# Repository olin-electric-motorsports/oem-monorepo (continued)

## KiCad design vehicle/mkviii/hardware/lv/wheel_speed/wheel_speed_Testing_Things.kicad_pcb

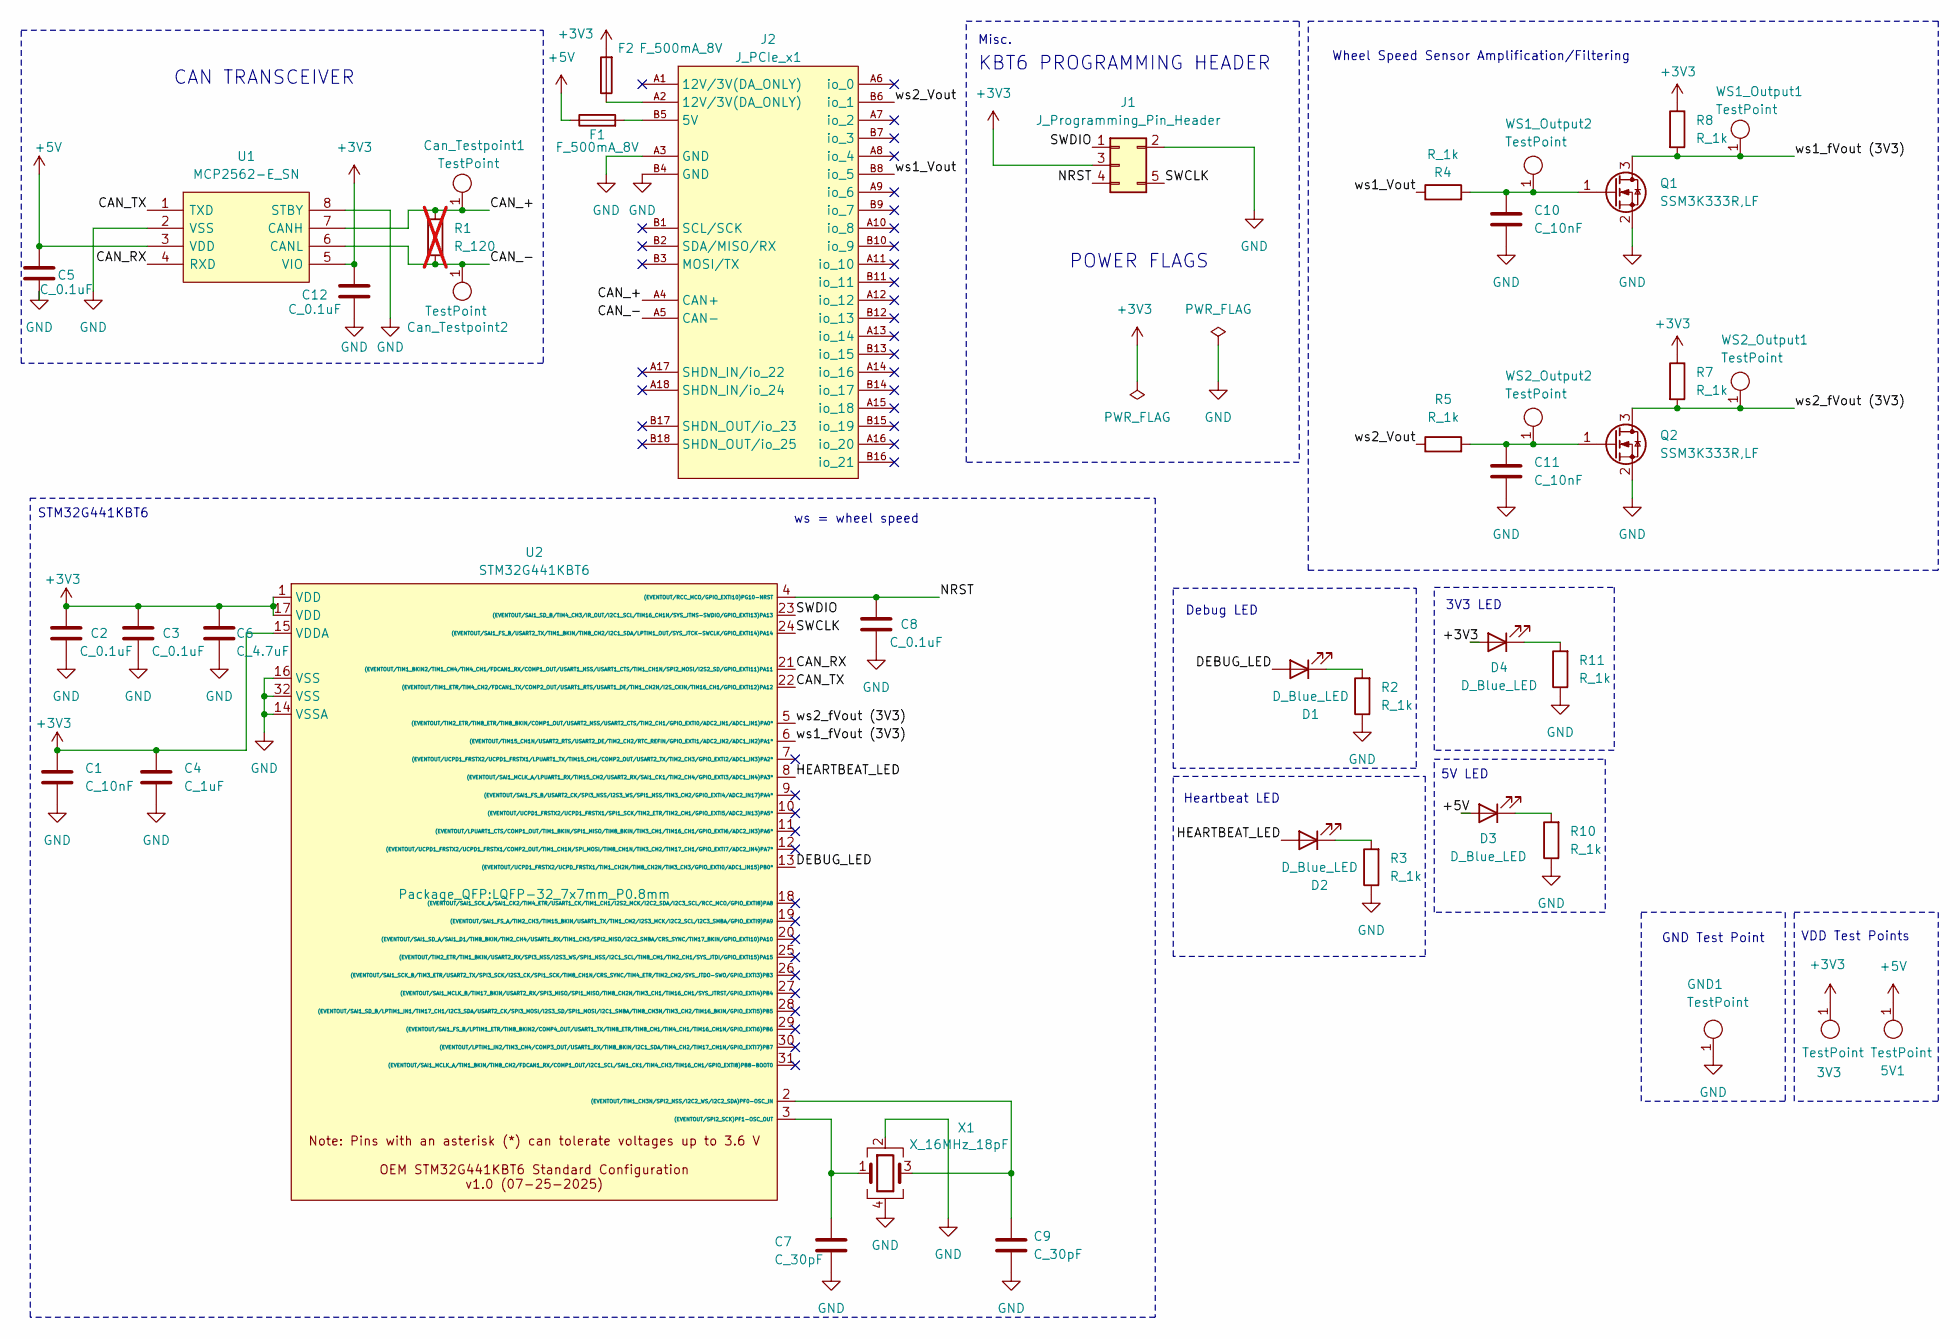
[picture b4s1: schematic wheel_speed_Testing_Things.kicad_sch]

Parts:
3V3, 5V1: TestPoint; TP_Hook_SMD; MPN 5019
C1, C10, C11: C_10nF; C_0603_1608Metric; MPN CL10B103KB8NNNC
C2, C3, C8: C_0.1uF; C_0603_1608Metric; MPN CL10B104KB8NNWC
C4: C_1uF; C_0603_1608Metric; MPN CL10B105KA8NNNC
C5, C12: C_0.1uF; C_0603_1608Metric; MPN C0603C104Z4VACTU
C6: C_4.7uF; C_0603_1608Metric; MPN GRT188R61E475ME13D
C7, C9: C_30pF; C_0603_1608Metric; MPN CML0603C0G300JT50V
Can_Testpoint1, Can_Testpoint2: TestPoint; TP_Hook_SMD; MPN 5019
D1, D2, D3, D4: D_Blue_LED; D_0805_2012Metric; MPN LTST-C171TBKT
F1, F2: F_500mA_8V; Fuse_1206_3216Metric; MPN 0ZCJ0050FF2G
GND1: TestPoint; TP_Hook_SMD; MPN 5019
J1: J_Programming_Pin_Header; J_Programming_Pin_Header_Keyed
J2: J_PCIe_x1; J_PCIe_x1_Key; MPN 2-1761465-1
Q1, Q2: SSM3K333R,LF; SOT-23-3
R1: R_120; R_0603_1608Metric; MPN RC0603FR-13120RL; not fitted
R2, R3, R4, R5, R7, R8, R10, R11: R_1k; R_0603_1608Metric; MPN RMCF0603FT1K00 (or ERJ-3GEYJ102V)
U1: MCP2562-E_SN; SOIC127P600X175-8N; Manufacturer_Part_Number MCP2562-E/SN; Mouser Part Number 579-MCP2562-E/SN
U2: STM32G441KBT6; LQFP-32_7x7mm_P0.8mm
WS1_Output1, WS1_Output2, WS2_Output1, WS2_Output2: TestPoint; TP_Hook_SMD; MPN 5019
X1: X_16MHz_18pF; FA238160000MBC0 (X_16MHz_18pF_SMD - FA-238_16.0000MB-C0); MPN FA-238 16.0000MB-C0

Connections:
+3V3: 3V3.1, C1.1, C2.1, C3.1, C4.1, C6.1, C12.2, D4.2 (A), F2.2, J1.3, R7.1, R8.1, U1.5 (VIO), U2.1 (VDD), U2.15 (VDDA), U2.17 (VDD)
+5V: 5V1.1, C5.2, D3.2 (A), F1.1, U1.3 (VDD)
/CAN_+: Can_Testpoint1.1, J2.A4 (CAN+), R1.1, U1.7 (CANH)
/CAN_-: Can_Testpoint2.1, J2.A5 (CAN-), R1.2, U1.6 (CANL)
/CAN_RX: U1.4 (RXD), U2.21 ((EVENTOUT/TIM1_BKIN2/TIM1_CH4/TIM4_CH1/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)
/CAN_TX: U1.1 (TXD), U2.22 ((EVENTOUT/TIM1_ETR/TIM4_CH2/FDCAN1_TX/C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)
/DEBUG_LED: D1.2 (A), U2.13 ((EVENTOUT/UCPD1_FRSTX2/UCPD_FRSTX1/TIM1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)
/HEARTBEAT_LED: D2.2 (A), U2.8 ((EVENTOUT/SAI1_MCLK_A/LPUART1_RX/TIM15_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)
/NRST: C8.1, J1.4, U2.4 ((EVENTOUT/RCC_MCO/GPIO_EXTI10)PG10-NRST)
/SWCLK: J1.5, U2.24 ((EVENTOUT/SAI1_FS_B/USART2_TX/TIM1_BKIN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)
/SWDIO: J1.1, U2.23 ((EVENTOUT/SAI1_SD_B/TIM4_CH3/IR_OUT/I2C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)
/ws1_Vout: J2.B8 (io_5), R4.1
/ws1_fVout (3V3): Q1.3 (D), R8.2, U2.6 ((EVENTOUT/TIM15_CH1N/USART2_RTS/USART2_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), WS1_Output1.1
/ws2_Vout: J2.B6 (io_1), R5.1
/ws2_fVout (3V3): Q2.3 (D), R7.2, U2.5 ((EVENTOUT/TIM2_ETR/TIM8_ETR/TIM8_BKIN/C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), WS2_Output1.1
GND: C1.2, C2.2, C3.2, C4.2, C5.1, C6.2, C7.2, C8.2, C9.2, C10.2, C11.2, C12.1, GND1.1, J1.2, J2.A3 (GND), J2.B4 (GND), Q1.2 (S), Q2.2 (S), R2.1, R3.1, R10.1, R11.1, U1.2 (VSS), U1.8 (STBY), U2.14 (VSSA), U2.16 (VSS), U2.32 (VSS), X1.2, X1.4
unnamed: D1.1 (K), R2.2
unnamed: D2.1 (K), R3.2
unnamed: D3.1 (K), R10.2
unnamed: D4.1 (K), R11.2
unnamed: F2.1, J2.A2 (12V/3V(DA_ONLY))
unnamed: F1.2, J2.B5 (5V)
unnamed: C10.1, Q1.1 (G), R4.2, WS1_Output2.1
unnamed: C11.1, Q2.1 (G), R5.2, WS2_Output2.1
unnamed: C7.1, U2.3 ((EVENTOUT/SPI2_SCK)PF1-OSC_OUT), X1.1
unnamed: C9.1, U2.2 ((EVENTOUT/TIM1_CH3N/SPI2_NSS/I2C2_WS/I2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), X1.3

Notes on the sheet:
Debug LED
Wheel Speed Sensor Amplification/Filtering
KBT6 PROGRAMMING HEADER
3V3 LED
ws = wheel speed
VDD Test Points
STM32G441KBT6
GND Test Point
Misc.
POWER FLAGS
5V LED
CAN TRANSCEIVER
Heartbeat LED

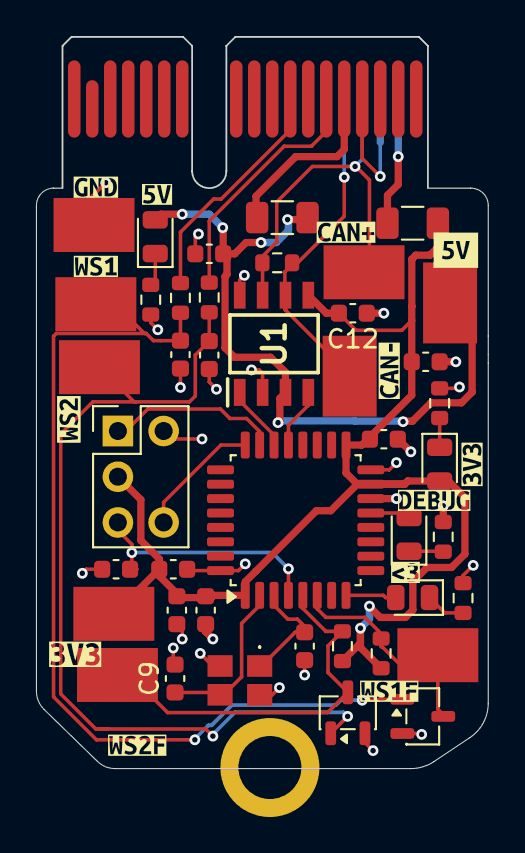
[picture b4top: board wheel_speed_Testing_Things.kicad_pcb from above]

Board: 2 copper layers, 25.1 x 40.6 mm, 57 parts (1 on the bottom side), 26 nets.

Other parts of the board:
kibuzzard-6AFB7296: G***; kibuzzard-6AFB7296
kibuzzard-6B0184AC: G***; kibuzzard-6B0184AC
kibuzzard-6B0184C3: G***; kibuzzard-6B0184C3
kibuzzard-6B0184D5: G***; kibuzzard-6B0184D5
kibuzzard-6B0184F9: G***; kibuzzard-6B0184F9
kibuzzard-6B0185A5: G***; kibuzzard-6B0185A5
kibuzzard-6B01848C: G***; kibuzzard-6B01848C
kibuzzard-6B01849E: G***; kibuzzard-6B01849E
kibuzzard-6B01852D: G***; kibuzzard-6B01852D
kibuzzard-6B01855D: G***; kibuzzard-6B01855D
kibuzzard-6B01859A: G***; kibuzzard-6B01859A
kibuzzard-6B018509: G***; kibuzzard-6B018509
kibuzzard-6B018514: G***; kibuzzard-6B018514
kibuzzard-6B018548: G***; kibuzzard-6B018548

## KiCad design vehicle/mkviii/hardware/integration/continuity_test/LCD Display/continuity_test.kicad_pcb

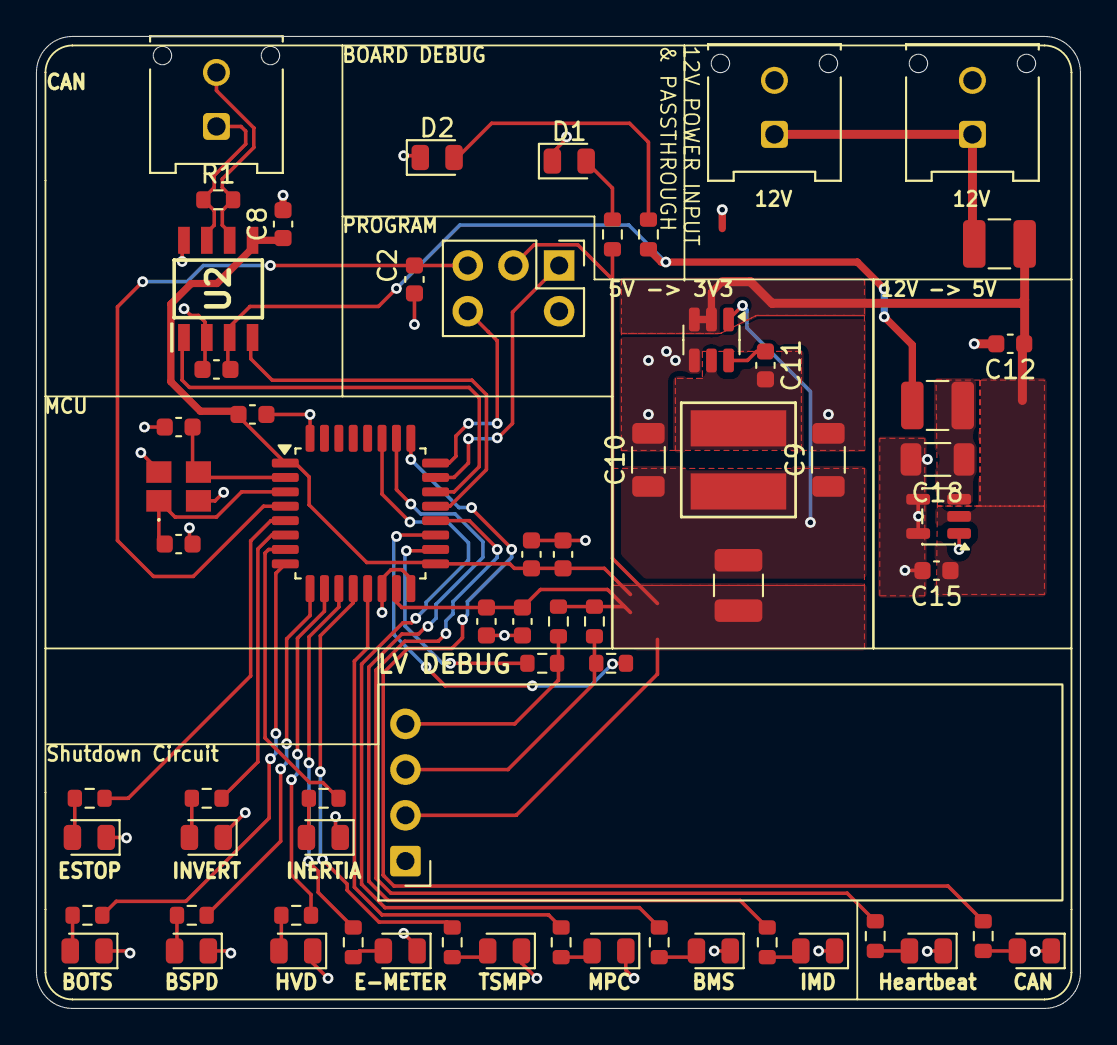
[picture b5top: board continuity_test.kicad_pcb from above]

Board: 2 copper layers, 58.0 x 54.0 mm, 65 parts (0 on the bottom side), 50 nets.

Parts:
C1, C2, C5, C6, C11: C_0.1uF; C_0603_1608Metric
C3: C_10nF; C_0603_1608Metric
C4: C_1uF; C_0603_1608Metric
C7: C_4.7uF; C_0603_1608Metric
C8, C15: C_0.1uF_16V; C_0603_1608Metric
C9, C10: C_22uF; C_1206_3216Metric
C12: C_10uF; C_0603_1608Metric
C13, C14: C_30pF; C_0603_1608Metric
C18: C_1uF; C_1206_3216Metric
D1: 3V3 POWER; D_0805_2012Metric
D2: 5V POWER; D_0805_2012Metric
D3, D4, D5, D6, D7, D8, D9, D10, D11, D12, D13, D14, D15: SOME_SHUTDOWN_NODE; D_0805_2012Metric
F1, F2, F3: F_500mA_16V; Fuse_1210_3225Metric
J1, J3, J4: Conn_01x02_Pin; Molex_Micro-Fit_3.0_43045-0212_2x01_P3.00mm_Vertical
J2: Programming_Pin_Header; J_Programming_Pin_Header_Keyed
L1: L_3.9uH; IND_BOURNS_SRR5018 (L_3.9uH_2A_55m_SMD)
R1: R_120; R_0603_1608Metric
R2, R3, R6, R7, R8, R9, R10, R11, R12, R13, R14, R15, R16, R17, R18: R_1K; R_0603_1608Metric
R4, R5: R_330_0.1W; R_0603_1608Metric
R19, R20: R_4.7k; R_0603_1608Metric
U1: STM32G441KBT6; LQFP-32_7x7mm_P0.8mm
U2: MCP2562-E_SN; SOIC127P600X175-8N
U3: AP63203WU-7; SOT-23-6
U4: TLV70450DBVR; SOT-23-5
U5: ER_OLEDM0.91_1x-I2C
Y1: X_Crystal_16MHz_18pF; FA238160000MBC0 (X_16MHz_18pF_SMD - FA-238_16.0000MB-C0)

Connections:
+3V3: C3.1, C4.1, C5.1, C6.1, C7.1, C8.1, F2.2, J2.3, R2.1, R19.1, R20.1, U1.1 (VDD), U1.15 (VDDA), U1.17 (VDD), U2.5 (VIO), U5.2 (VCC)
+5V: C1.2, F3.2, R3.1, U2.3 (VDD)
+12V: C12.1, C15.1, F1.1, U3.2 (EN), U3.3 (VIN), U4.2 (IN)
/CAN_+: J4.1, R1.1, U2.7 (CANH)
/CAN_-: J4.2, R1.2, U2.6 (CANL)
/CAN_RX: U1.21 ((FDCAN1_RX/GPIO_EXTI11)PA11), U2.4 (RXD)
/CAN_TX: U1.22 ((FDCAN1_TX/GPIO_EXTI12)PA12), U2.1 (TXD)
/I2C_SCL: R4.1, U1.19 ((TIM2_CH3/TIM15_BKIN/USART1_TX/GPIO_EXT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)
/I2C_SDA: R5.1, U1.18 ((TIM4_ETR/USART1_CK/GPIO_EXTI8)PA8)
/LED0: R6.1, U1.5 ((TIM2_ETR/TIM2_CH1/GPIO_EXTI0/ADC2_IN1/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)
/LED1: R7.1, U1.6 ((TIM15_CH1N/TIM2_CH2/GPIO_EXTI1/ADC2_IN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)
/LED2: R8.1, U1.7 ((TIM15_CH1/USART2_TX/TIM2_CH3/GPIO_EXTI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)
/LED3: R9.1, U1.8 ((TIM15_CH2/USART2_RX/TIM2_CH4/GPIO_EXTI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)
/LED4: R10.1, U1.9 ((USART2_CK/TIM3_CH2/GPIO_EXTI4/ADC2_IN1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)
/LED5: R11.1, U1.10 ((TIM2_ETR/TIM2_CH1/GPIO_EXTI5/ADC2_IN13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)
/LED6: R12.1, U1.11 ((TIM3_CH1/TIM16_CH1/GPIO_EXTI6/ADC2_IN3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)
/LED7: R13.1, U1.12 ((TIM3_CH2/TIM17_CH1/GPIO_EXTI7/ADC2_IN4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)
/LED8: R14.1, U1.13 ((TIM3_CH3/GPIO_EXTI0/ADC1_IN15)PB0*)
/LED9: R15.1, U1.27 ((TIM17_BKIN/SPI1_MISO/TIM3_CH1/TIM16_CH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)
/LED10: R16.1, U1.26 ((TIM3_ETR/SPI1_SCK/TIM4_ETR/TIM2_CH2/GP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)
/LED11: R17.1, U1.20 ((TIM2_CH4/USART1_RX/TIM17_BKIN/GPIO_EXT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)
/LED12: R18.1, U1.25 ((TIM2_ETR/TIM2_CH1/GPIO_EXTI15)PA15)
/NRST: C2.1, J2.4, U1.4 ((GPIO_EXTI10)PG10-NRST)
/SWCLK: J2.5, U1.24 ((SYS_JTCK-SWCLK/GPIO_EXTI14)PA14)
/SWDIO: J2.1, U1.23 ((SYS_JTMS-SWDIO/GPIO_EXTI13)PA13)
/V_INPUT: F1.2, J1.1, J3.1
GND: C1.1, C2.2, C3.2, C4.2, C5.2, C6.2, C7.2, C8.2, C9.2, C10.2, C12.2, C13.2, C14.2, C15.2, C18.2, D1.1 (K), D2.1 (K), D3.1 (K), D4.1 (K), D5.1 (K), D6.1 (K), D7.1 (K), D8.1 (K), D9.1 (K), D10.1 (K), D11.1 (K), D12.1 (K), D13.1 (K), D14.1 (K), D15.1 (K), J1.2, J2.2, J3.2, U1.14 (VSSA), U1.16 (VSS), U1.32 (VSS), U2.2 (VSS), U2.8 (STBY), U3.4 (GND), U4.1 (GND), U4.4 (NC_1), U4.5 (NC_2), U5.1 (GND), Y1.2, Y1.4
unnamed: D1.2 (A), R2.2
unnamed: D2.2 (A), R3.2
unnamed: D3.2 (A), R6.2
unnamed: D4.2 (A), R7.2
unnamed: D5.2 (A), R8.2
unnamed: D6.2 (A), R9.2
unnamed: D7.2 (A), R10.2
unnamed: D8.2 (A), R11.2
unnamed: D9.2 (A), R12.2
unnamed: D10.2 (A), R13.2
unnamed: D11.2 (A), R14.2
unnamed: D12.2 (A), R15.2
unnamed: D13.2 (A), R16.2
unnamed: D14.2 (A), R17.2
unnamed: D15.2 (A), R18.2
unnamed: C13.1, U1.2 (PF0-OSC_IN), Y1.3
unnamed: C14.1, U1.3 (PF1-OSC_OUT), Y1.1
unnamed: C11.1, U3.6 (BST)
unnamed: C9.1, C10.1, F2.1, L1.2, U3.1 (FB)
unnamed: C11.2, L1.1, U3.5 (SW)
unnamed: C18.1, F3.1, U4.3 (OUT)
unnamed: R4.2, R19.2, U5.3 (SCL)
unnamed: R5.2, R20.2, U5.4 (SDA)

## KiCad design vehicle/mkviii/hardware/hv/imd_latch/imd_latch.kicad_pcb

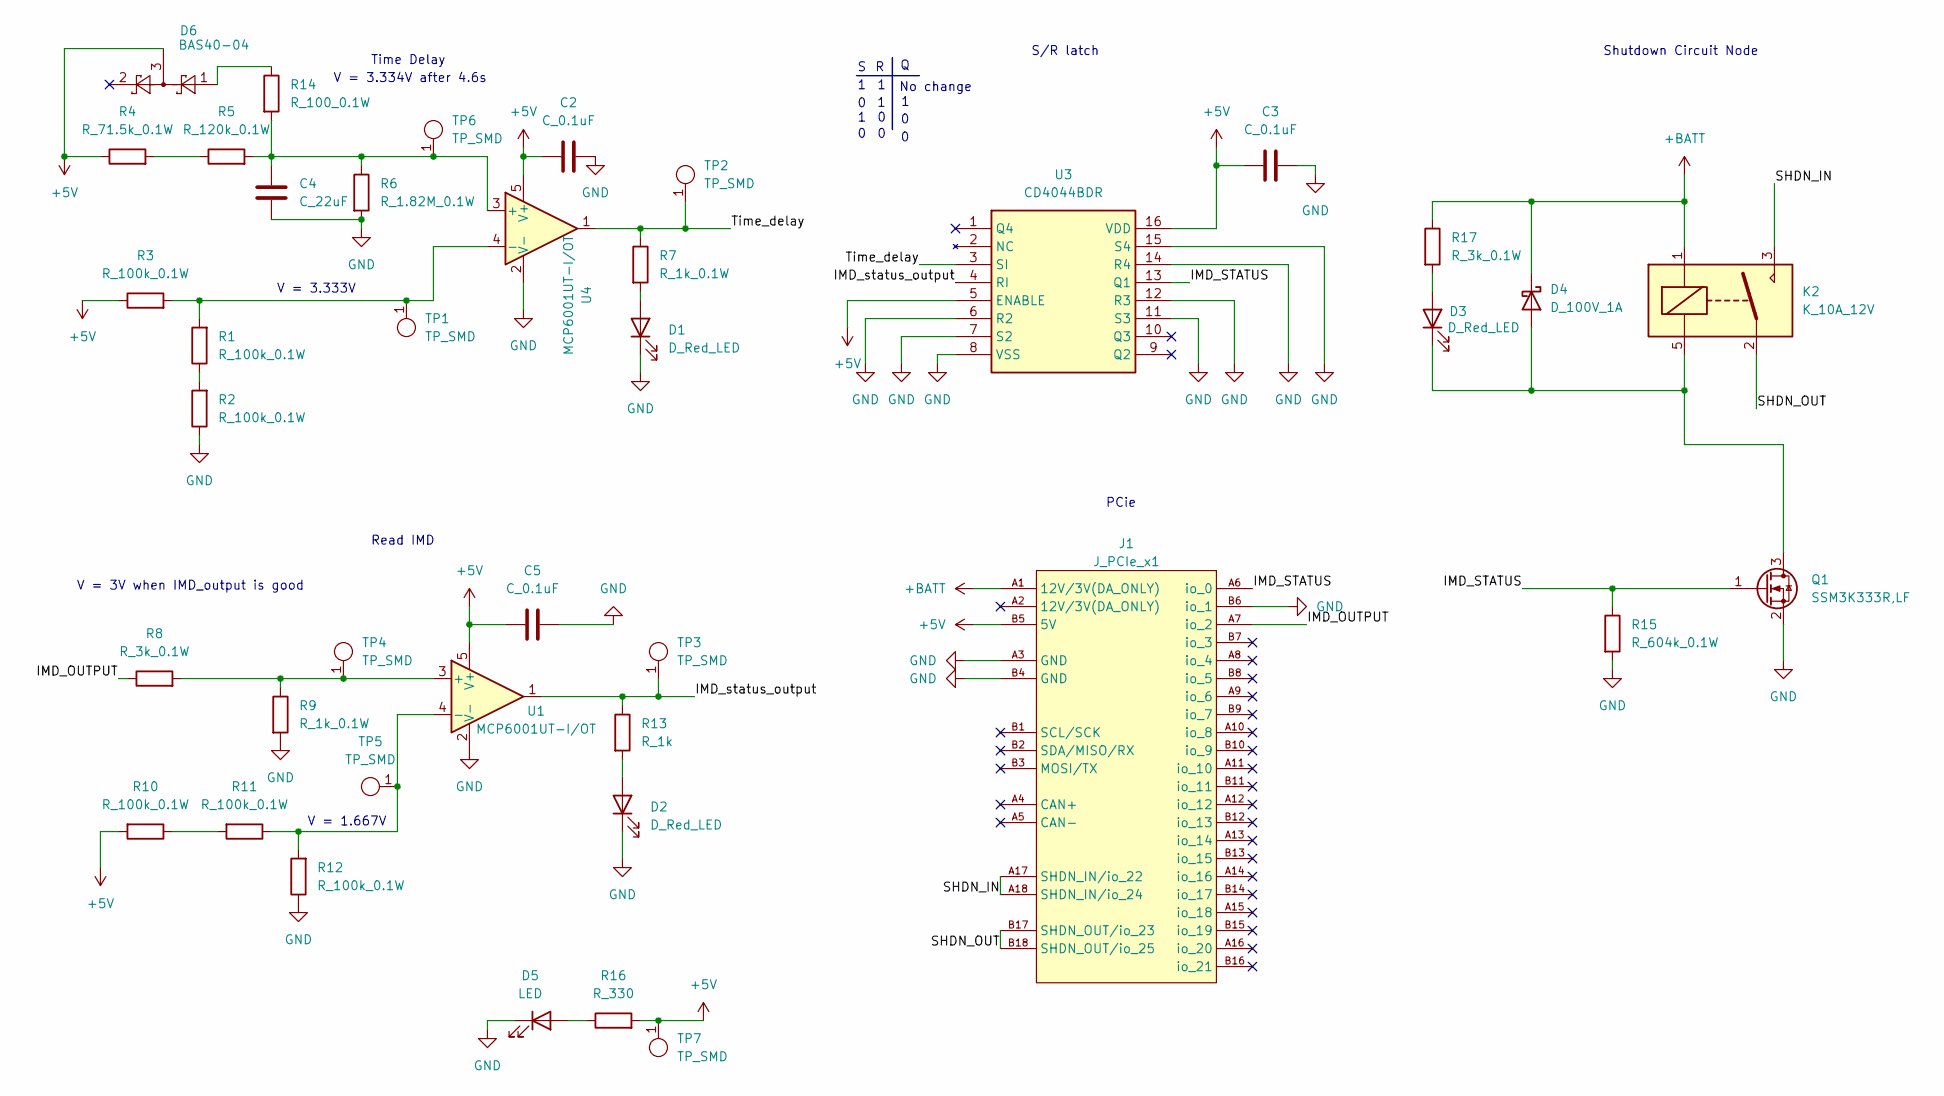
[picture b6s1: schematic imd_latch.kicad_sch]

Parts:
C2, C3, C5: C_0.1uF; C_0603_1608Metric; MPN C0603C104Z4VACTU
C4: C_22uF; C_1206_3216Metric; MPN CL31A226KAHNNNE
D1, D2, D3: D_Red_LED; D_0805_2012Metric; MPN LTST-C171KRKT
D4: D_100V_1A; SODFL3718X102N (D_Schottky_100V_1A_SMD - SS110LW); MPN SS110LW
D5: LED; D_0805_2012Metric; MPN QBLP631-IW
D6: BAS40-04; SOT-23
J1: J_PCIe_x1; J_PCIe_x1_Key; MPN 2-1761465-1
K2: K_10A_12V; G5Q1A4DC24 (K_SPST-NO_10A_12V_TH - G5Q-1A4-DC12); MPN G5Q-1A4 DC12
Q1: SSM3K333R,LF; SOT-23-3
R1, R2, R3, R10, R11, R12: R_100k_0.1W; R_0603_1608Metric; MPN RMCF0603FT100K
R4: R_71.5k_0.1W; R_0603_1608Metric; MPN RMCF0603FT71K5
R5: R_120k_0.1W; R_0603_1608Metric; MPN RC0603FR-13120KL
R6: R_1.82M_0.1W; R_0603_1608Metric; MPN RMCF0603FT1M82
R7, R9: R_1k_0.1W; R_0603_1608Metric; MPN RMCF0603FT1K00 (or ERJ-3GEYJ102V)
R8, R17: R_3k_0.1W; R_0603_1608Metric; MPN RC0603FR-103KL
R13: R_1k; R_0603_1608Metric; MPN RMCF0603FT1K00 (or ERJ-3GEYJ102V)
R14: R_100_0.1W; R_0603_1608Metric; MPN RMCF0603FT100R
R15: R_604k_0.1W; R_0603_1608Metric; MPN RMCF0603FT604K
R16: R_330; R_0603_1608Metric; MPN RMCF0603FT330R (or WR06X3300FTL)
TP1, TP2, TP3, TP4, TP5, TP6, TP7: TP_SMD; TP_Hook_SMD; MPN 5019
U1, U4: MCP6001UT-I/OT; SOT-23-5; MPN MCP6001UT-I/OT
U3: CD4044BDR; SOIC127P600X175-16N (U_Quad-NAND-RS-Latch_CD4044BDR_16-SOIC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; MPN CD4044BDR

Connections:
+5V: C2.1, C3.1, C5.2, D6.3, J1.B5 (5V), R3.1, R4.1, R10.2, R16.2, TP7.1, U1.5 (V+), U3.5 (ENABLE), U3.16 (VDD), U4.5 (V+)
+BATT: D4.1 (K), J1.A1 (12V/3V(DA_ONLY)), K2.1, R17.1
/<NO NET>: J1.A7 (io_2), R8.1
/IMD_STATUS: J1.A6 (io_0), Q1.1 (G), R15.1, U3.13 (Q1)
/IMD_status_output: R13.1, TP3.1, U1.1, U3.4 (RI)
/SHDN_IN: J1.A17 (SHDN_IN/io_22), J1.A18 (SHDN_IN/io_24), K2.3
/SHDN_OUT: J1.B17 (SHDN_OUT/io_23), J1.B18 (SHDN_OUT/io_25), K2.2
/Time_delay: R7.1, TP2.1, U3.3 (SI), U4.1
GND: C2.2, C3.2, C4.2, C5.1, D1.1 (K), D2.1 (K), D5.1 (K), J1.A3 (GND), J1.B4 (GND), J1.B6 (io_1), Q1.2 (S), R2.1, R6.2, R9.2, R12.1, R15.2, U1.2 (V-), U3.6 (R2), U3.7 (S2), U3.8 (VSS), U3.11 (S3), U3.12 (R3), U3.14 (R4), U3.15 (S4), U4.2 (V-)
unnamed: D1.2 (A), R7.2
unnamed: D2.2 (A), R13.2
unnamed: D3.2 (A), R17.2
unnamed: D3.1 (K), D4.2 (A), K2.5, Q1.3 (D)
unnamed: D5.2 (A), R16.1
unnamed: D6.1, R14.1
unnamed: R1.1, R2.2
unnamed: R4.2, R5.1
unnamed: R10.1, R11.2
unnamed: R8.2, R9.1, TP4.1, U1.3 (+)
unnamed: R11.1, R12.2, TP5.1, U1.4 (-)
unnamed: C4.1, R5.2, R6.1, R14.2, TP6.1, U4.3 (+)
unnamed: R1.2, R3.2, TP1.1, U4.4 (-)

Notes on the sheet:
Shutdown Circuit Node
S/R latch
No change
V = 3.334V after 4.6s
Time Delay
Read IMD
PCie
V = 3.333V
V = 3V when IMD_output is good
V = 1.667V

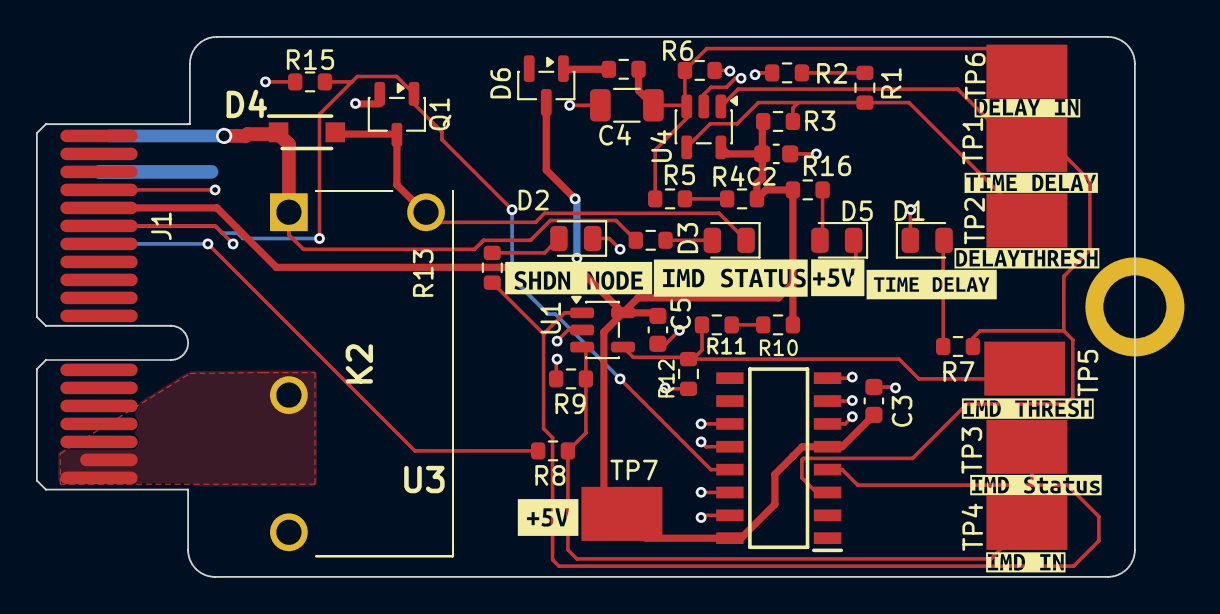
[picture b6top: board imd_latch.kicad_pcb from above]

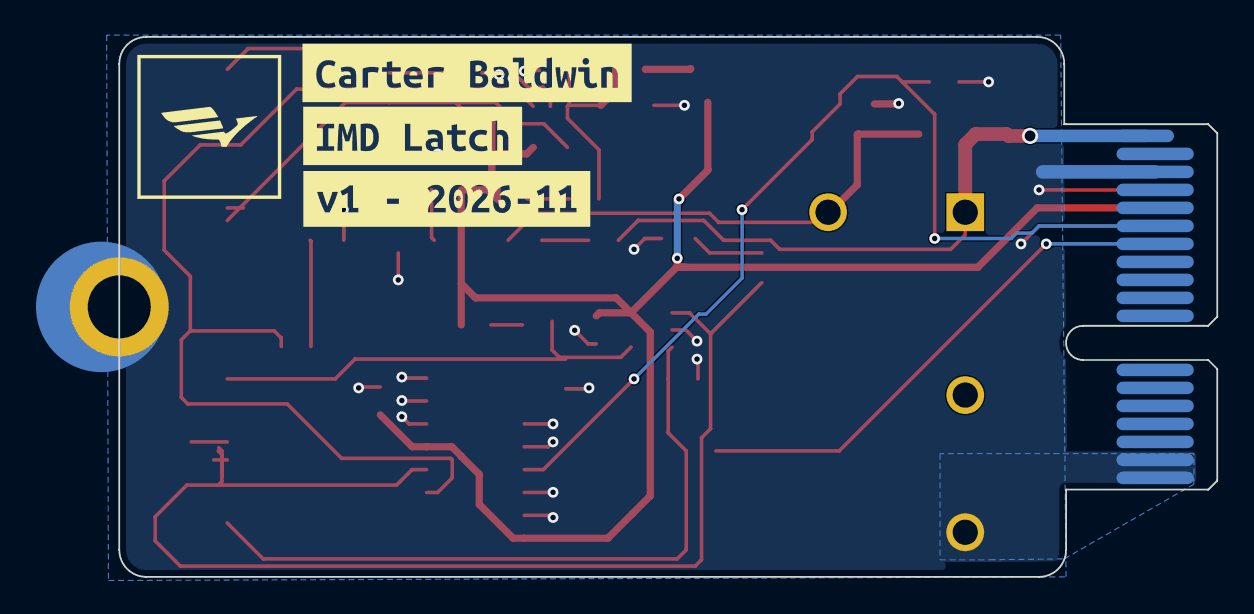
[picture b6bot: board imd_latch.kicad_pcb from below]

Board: 2 copper layers, 61.0 x 30.0 mm, 54 parts (3 on the bottom side), 22 nets.

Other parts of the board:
kibuzzard-6AFBBCFF: G***; kibuzzard-6AFBBCFF
kibuzzard-6AFCD9A5: G***; kibuzzard-6AFCD9A5
kibuzzard-6AFDBAFF: G***; kibuzzard-6AFDBAFF
kibuzzard-6AFDBEA3: G***; kibuzzard-6AFDBEA3
kibuzzard-6AFDC0E0: G***; kibuzzard-6AFDC0E0
kibuzzard-6AFDC1E5: G***; kibuzzard-6AFDC1E5
kibuzzard-6AFDC9E2: G***; kibuzzard-6AFDC9E2
kibuzzard-6AFDC9E7: G***; kibuzzard-6AFDC9E7
kibuzzard-6AFDC12F: G***; kibuzzard-6AFDC12F
kibuzzard-6AFDC58C: G***; kibuzzard-6AFDC58C
kibuzzard-6AFDC564: G***; kibuzzard-6AFDC564
kibuzzard-6AFDC608: G***; kibuzzard-6AFDC608
kibuzzard-6AFDCAAF: G***; kibuzzard-6AFDCAAF
kibuzzard-6B015E83: G***; kibuzzard-6B015E83

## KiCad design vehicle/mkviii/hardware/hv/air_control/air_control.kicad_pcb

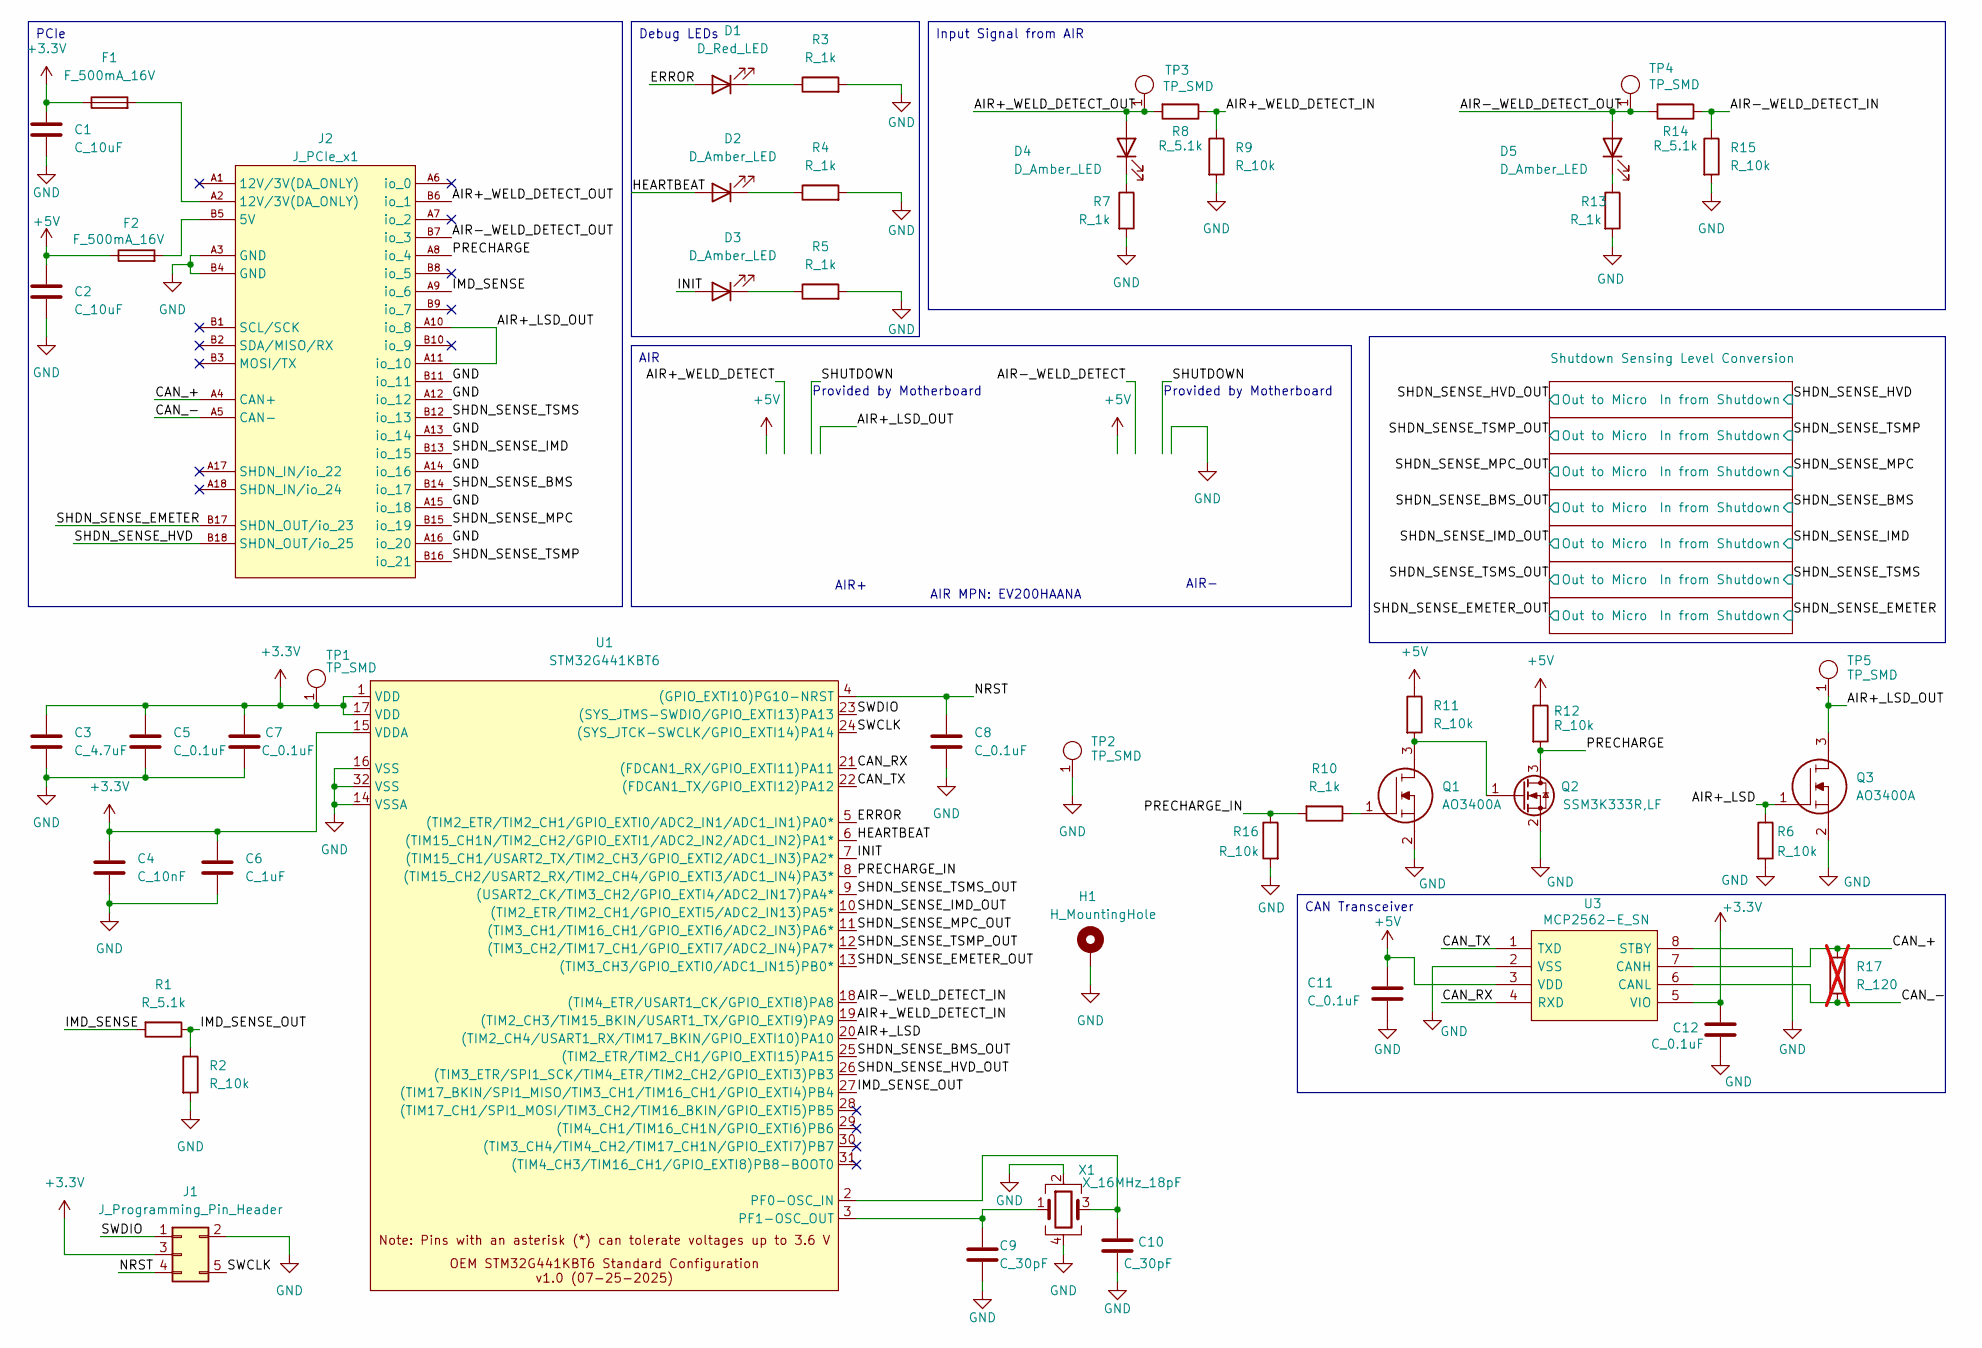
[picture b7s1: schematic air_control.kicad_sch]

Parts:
C1, C2: C_10uF; C_0603_1608Metric; MPN GRM188D71A106KA73D
C3: C_4.7uF; C_0603_1608Metric; MPN GRT188R61E475ME13D
C4: C_10nF; C_0603_1608Metric; MPN CL10B103KB8NNNC
C5, C7, C8, C11, C12: C_0.1uF; C_0603_1608Metric; MPN CL10B104KB8NNWC
C6: C_1uF; C_0603_1608Metric; MPN CL10B105KA8NNNC
C9, C10: C_30pF; C_0603_1608Metric; MPN CML0603C0G300JT50V
D1: D_Red_LED; D_0805_2012Metric; MPN LTST-C171KRKT
D2, D3, D4, D5: D_Amber_LED; D_0805_2012Metric; MPN LTST-C171AKT
F1, F2: F_500mA_16V; Fuse_1210_3225Metric; MPN 0ZCH0050FF2G
H1: H_MountingHole
J1: J_Programming_Pin_Header; J_Programming_Pin_Header_Keyed
J2: J_PCIe_x1; J_PCIe_x1_Key; MPN 2-1761465-1
Q1, Q3: AO3400A; Q_MOSFET_AO3400A; Manufacturer_Part_Number AO3400A
Q2: SSM3K333R,LF; SOT-23-3
R1, R8, R14: R_5.1k; R_0603_1608Metric; MPN CR0603AFX-5101EAS
R2, R6, R9, R11, R12, R15, R16: R_10k; R_0603_1608Metric; MPN RMCF0603FT10K0
R3, R4, R5, R7, R10, R13: R_1k; R_0603_1608Metric; MPN RMCF0603FT1K00 (or ERJ-3GEYJ102V)
R17: R_120; R_0603_1608Metric; MPN RC0603FR-13120RL; not fitted
TP1, TP2, TP3, TP4, TP5: TP_SMD; TP_Hook_SMD; MPN 5019
U1: STM32G441KBT6; LQFP-32_7x7mm_P0.8mm
U3: MCP2562-E_SN; SOIC127P600X175-8N; Manufacturer_Part_Number MCP2562-E/SN; Mouser Part Number 579-MCP2562-E/SN
X1: X_16MHz_18pF; FA238160000MBC0 (X_16MHz_18pF_SMD - FA-238_16.0000MB-C0); MPN FA-238 16.0000MB-C0

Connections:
+3.3V: C1.1, C3.1, C4.1, C5.1, C6.1, C7.1, C12.1, F1.1, J1.3, TP1.1, U1.1 (VDD), U1.15 (VDDA), U1.17 (VDD), U3.5 (VIO); also elsewhere on the board
+5V: C2.1, C11.1, F2.1, R11.1, R12.1, U3.3 (VDD)
/AIR+_LSD: Q3.1, R6.1, U1.20 ((TIM2_CH4/USART1_RX/TIM17_BKIN/GPIO_EXT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)
/AIR+_LSD_OUT: J2.A10 (io_8), J2.A11 (io_10), Q3.3, TP5.1
/AIR+_WELD_DETECT_IN: R8.1, R9.1, U1.19 ((TIM2_CH3/TIM15_BKIN/USART1_TX/GPIO_EXT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)
/AIR+_WELD_DETECT_OUT: D4.2 (A), J2.B6 (io_1), R8.2, TP3.1
/AIR-_WELD_DETECT_IN: R14.1, R15.1, U1.18 ((TIM4_ETR/USART1_CK/GPIO_EXTI8)PA8)
/AIR-_WELD_DETECT_OUT: D5.2 (A), J2.B7 (io_3), R14.2, TP4.1
/CAN_+: J2.A4 (CAN+), R17.1, U3.7 (CANH)
/CAN_-: J2.A5 (CAN-), R17.2, U3.6 (CANL)
/CAN_RX: U1.21 ((FDCAN1_RX/GPIO_EXTI11)PA11), U3.4 (RXD)
/CAN_TX: U1.22 ((FDCAN1_TX/GPIO_EXTI12)PA12), U3.1 (TXD)
/ERROR: D1.2 (A), U1.5 ((TIM2_ETR/TIM2_CH1/GPIO_EXTI0/ADC2_IN1/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)
/HEARTBEAT: D2.2 (A), U1.6 ((TIM15_CH1N/TIM2_CH2/GPIO_EXTI1/ADC2_IN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)
/IMD_SENSE: J2.A9 (io_6), R1.2
/IMD_SENSE_OUT: R1.1, R2.1, U1.27 ((TIM17_BKIN/SPI1_MISO/TIM3_CH1/TIM16_CH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)
/INIT: D3.2 (A), U1.7 ((TIM15_CH1/USART2_TX/TIM2_CH3/GPIO_EXTI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)
/NRST: C8.1, J1.4, U1.4 ((GPIO_EXTI10)PG10-NRST)
/PRECHARGE: J2.A8 (io_4), Q2.3 (D), R12.2
/PRECHARGE_IN: R10.2, R16.1, U1.8 ((TIM15_CH2/USART2_RX/TIM2_CH4/GPIO_EXTI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)
/SHDN_SENSE_BMS: J2.B14 (io_17); also elsewhere on the board
/SHDN_SENSE_BMS_OUT: U1.25 ((TIM2_ETR/TIM2_CH1/GPIO_EXTI15)PA15); also elsewhere on the board
/SHDN_SENSE_EMETER: J2.B17 (SHDN_OUT/io_23); also elsewhere on the board
/SHDN_SENSE_EMETER_OUT: U1.13 ((TIM3_CH3/GPIO_EXTI0/ADC1_IN15)PB0*); also elsewhere on the board
/SHDN_SENSE_HVD: J2.B18 (SHDN_OUT/io_25); also elsewhere on the board
/SHDN_SENSE_HVD_OUT: U1.26 ((TIM3_ETR/SPI1_SCK/TIM4_ETR/TIM2_CH2/GP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); also elsewhere on the board
/SHDN_SENSE_IMD: J2.B13 (io_15); also elsewhere on the board
/SHDN_SENSE_IMD_OUT: U1.10 ((TIM2_ETR/TIM2_CH1/GPIO_EXTI5/ADC2_IN13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); also elsewhere on the board
/SHDN_SENSE_MPC: J2.B15 (io_19); also elsewhere on the board
/SHDN_SENSE_MPC_OUT: U1.11 ((TIM3_CH1/TIM16_CH1/GPIO_EXTI6/ADC2_IN3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); also elsewhere on the board
/SHDN_SENSE_TSMP: J2.B16 (io_21); also elsewhere on the board
/SHDN_SENSE_TSMP_OUT: U1.12 ((TIM3_CH2/TIM17_CH1/GPIO_EXTI7/ADC2_IN4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); also elsewhere on the board
/SHDN_SENSE_TSMS: J2.B12 (io_13); also elsewhere on the board
/SHDN_SENSE_TSMS_OUT: U1.9 ((USART2_CK/TIM3_CH2/GPIO_EXTI4/ADC2_IN1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); also elsewhere on the board
/SWCLK: J1.5, U1.24 ((SYS_JTCK-SWCLK/GPIO_EXTI14)PA14)
/SWDIO: J1.1, U1.23 ((SYS_JTMS-SWDIO/GPIO_EXTI13)PA13)
GND: C1.2, C2.2, C3.2, C4.2, C5.2, C6.2, C7.2, C8.2, C9.2, C10.2, C11.2, C12.2, H1.1 (1_1), J1.2, J2.A3 (GND), J2.A12 (io_12), J2.A13 (io_14), J2.A14 (io_16), J2.A15 (io_18), J2.A16 (io_20), J2.B4 (GND), J2.B11 (io_11), Q1.2, Q2.2 (S), Q3.2, R2.2, R3.2, R4.2, R5.2, R6.2, R7.2, R9.2, R13.2, R15.2, R16.2, TP2.1, U1.14 (VSSA), U1.16 (VSS), U1.32 (VSS), U3.2 (VSS), U3.8 (STBY), X1.2, X1.4; also elsewhere on the board
unnamed: D1.1 (K), R3.1
unnamed: D2.1 (K), R4.1
unnamed: D3.1 (K), R5.1
unnamed: D4.1 (K), R7.1
unnamed: D5.1 (K), R13.1
unnamed: F1.2, J2.A2 (12V/3V(DA_ONLY))
unnamed: F2.2, J2.B5 (5V)
unnamed: Q1.1, R10.1
unnamed: Q1.3, Q2.1 (G), R11.2
unnamed: C10.1, U1.2 (PF0-OSC_IN), X1.3
unnamed: C9.1, U1.3 (PF1-OSC_OUT), X1.1

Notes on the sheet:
AIR MPN: EV200HAANA
Provided by Motherboard
AIR+
AIR-
AIR
Debug LEDs
Input Signal from AIR
PCIe
CAN Transceiver

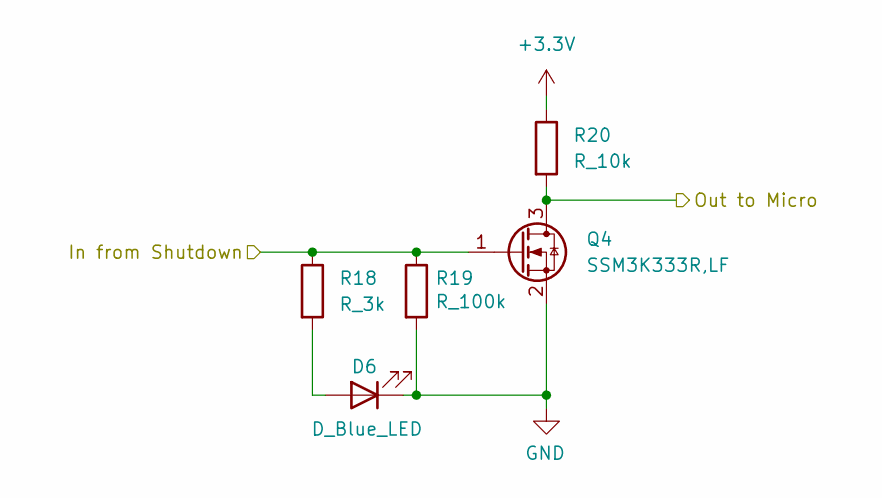
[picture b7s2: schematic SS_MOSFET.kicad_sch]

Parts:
D6: D_Blue_LED; D_0805_2012Metric; MPN LTST-C171TBKT
Q4: SSM3K333R,LF; SOT-23-3
R18: R_3k; R_0603_1608Metric; MPN RC0603FR-103KL
R19: R_100k; R_0603_1608Metric; MPN RMCF0603FT100K
R20: R_10k; R_0603_1608Metric; MPN RMCF0603FT10K0

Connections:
+3.3V: R20.1; also elsewhere on the board
/SHDN_SENSE_TSMP: Q4.1 (G), R18.1, R19.1; also elsewhere on the board
/SHDN_SENSE_TSMP_OUT: Q4.3 (D), R20.2; also elsewhere on the board
GND: D6.1 (K), Q4.2 (S), R19.2; also elsewhere on the board
unnamed: D6.2 (A), R18.2

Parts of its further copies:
D7, D8, D9, D10, D11, D12: D_Blue_LED; D_0805_2012Metric; MPN LTST-C171TBKT
Q5, Q6, Q7, Q8, Q9, Q10: SSM3K333R,LF; SOT-23-3
R21, R24, R27, R30, R33, R36: R_3k; R_0603_1608Metric; MPN RC0603FR-103KL
R22, R25, R28, R31, R34, R37: R_100k; R_0603_1608Metric; MPN RMCF0603FT100K
R23, R26, R29, R32, R35, R38: R_10k; R_0603_1608Metric; MPN RMCF0603FT10K0

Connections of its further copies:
+3.3V: R23.1, R26.1, R29.1, R32.1, R35.1, R38.1; also elsewhere on the board
/SHDN_SENSE_BMS: Q6.1 (G), R24.1, R25.1; also elsewhere on the board
/SHDN_SENSE_BMS_OUT: Q6.3 (D), R26.2; also elsewhere on the board
/SHDN_SENSE_EMETER: Q9.1 (G), R33.1, R34.1; also elsewhere on the board
/SHDN_SENSE_EMETER_OUT: Q9.3 (D), R35.2; also elsewhere on the board
/SHDN_SENSE_HVD: Q10.1 (G), R36.1, R37.1; also elsewhere on the board
/SHDN_SENSE_HVD_OUT: Q10.3 (D), R38.2; also elsewhere on the board
/SHDN_SENSE_IMD: Q7.1 (G), R27.1, R28.1; also elsewhere on the board
/SHDN_SENSE_IMD_OUT: Q7.3 (D), R29.2; also elsewhere on the board
/SHDN_SENSE_MPC: Q5.1 (G), R21.1, R22.1; also elsewhere on the board
/SHDN_SENSE_MPC_OUT: Q5.3 (D), R23.2; also elsewhere on the board
/SHDN_SENSE_TSMS: Q8.1 (G), R30.1, R31.1; also elsewhere on the board
/SHDN_SENSE_TSMS_OUT: Q8.3 (D), R32.2; also elsewhere on the board
GND: D7.1 (K), D8.1 (K), D9.1 (K), D10.1 (K), D11.1 (K), D12.1 (K), Q5.2 (S), Q6.2 (S), Q7.2 (S), Q8.2 (S), Q9.2 (S), Q10.2 (S), R22.2, R25.2, R28.2, R31.2, R34.2, R37.2; also elsewhere on the board
unnamed: D7.2 (A), R21.2
unnamed: D8.2 (A), R24.2
unnamed: D9.2 (A), R27.2
unnamed: D10.2 (A), R30.2
unnamed: D11.2 (A), R33.2
unnamed: D12.2 (A), R36.2
